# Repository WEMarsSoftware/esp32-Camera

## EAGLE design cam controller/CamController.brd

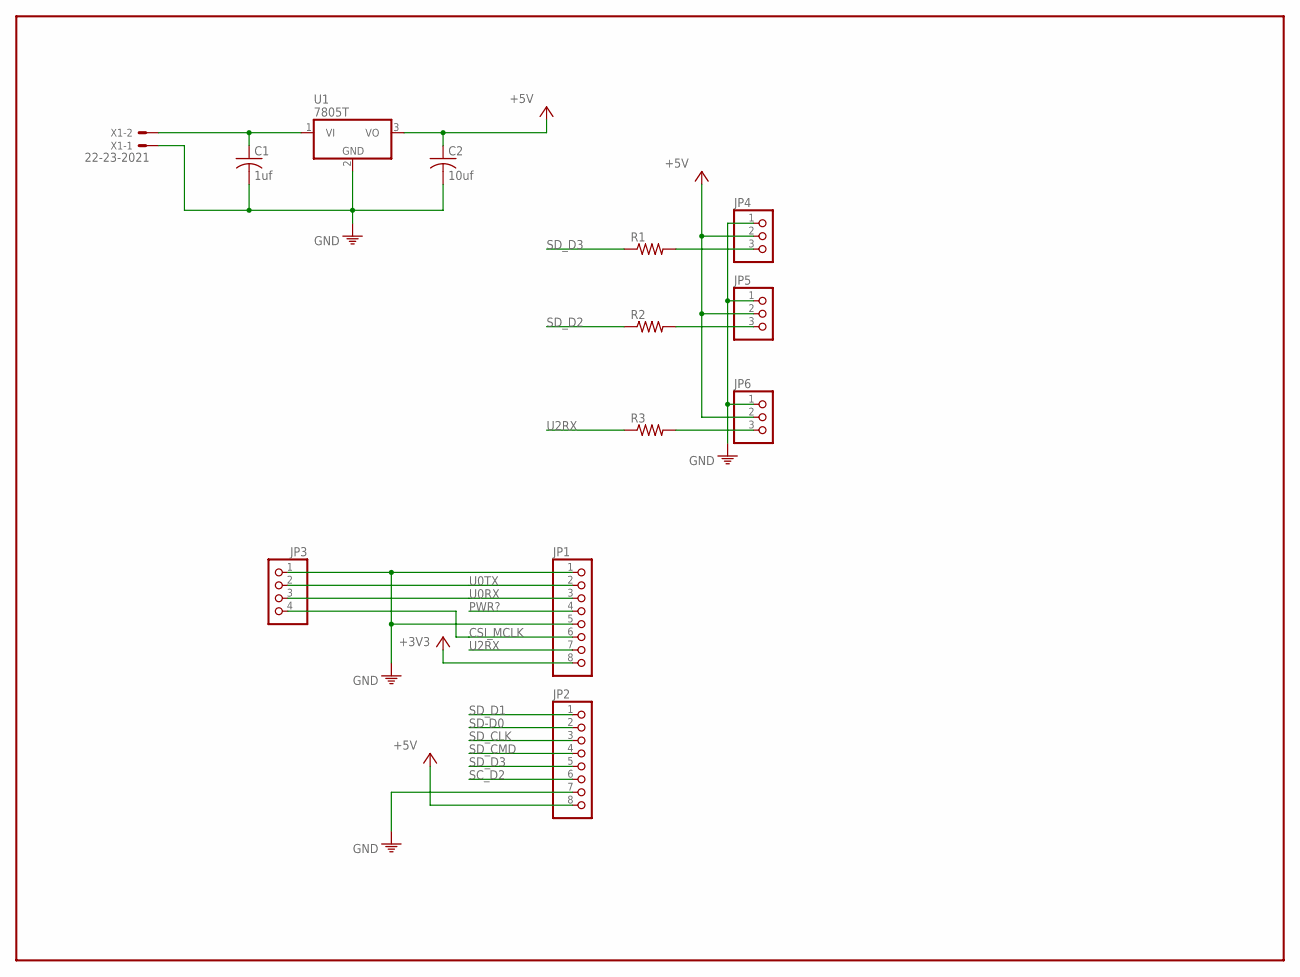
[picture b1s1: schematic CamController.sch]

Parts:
C1: 1uf; C025-040X050
C2: 10uf; C025-030X050
JP1, JP2: PINHD-1X8; 1X08
JP3: PINHD-1X4; 1X04
JP4, JP5, JP6: PINHD-1X3/90; 1X03/90
R1, R2, R3: R-US_0309/10; 0309/10
U1: 7805T; TO220H
X1: 22-23-2021

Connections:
+3V3: JP1.8
+5V: C2.1, JP2.8, JP4.2, JP5.2, JP6.2, U1.3 (VO)
CSI_MCLK: JP1.6, JP3.4
GND: C1.2, C2.2, JP1.1, JP1.5, JP2.7, JP3.1, U1.2 (GND), X1.1
unnamed: C1.1, U1.1 (VI), X1.2
unnamed: JP5.3, R2.2
unnamed: JP6.3, R3.2
PE: JP4.1, JP5.1, JP6.1
PWR?: JP1.4
SC_D2: JP2.6
SD-D0: JP2.2
SD_CLK: JP2.3
SD_CMD: JP2.4
SD_D1: JP2.1
SD_D2: R2.1
SD_D3: JP2.5, JP4.3, R1.1, R1.2
U0RX: JP1.3, JP3.3
U0TX: JP1.2, JP3.2
U2RX: JP1.7, R3.1

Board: 2 copper layers, 13 parts (2 on the bottom side), 11 nets, no tracks yet.

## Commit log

2019-07-13 start with origian CameraWEBSever code : modify to : have two pages one with controls the orther with just full sceen video and one butting to take you back to menu page chk out zooming and cropping
2019-07-15 removed all face recognition information: compiled
2019-08-02 test
2019-08-02 testing img sizing an position
2019-08-02 removve this to se it sizing changes
2019-08-02 made img big but lost controls
2019-08-02 pushed image all the way to right side
2019-08-05 set screen size to fixed size try to make larger smaller and flexable once sizes grow
2019-08-05 set size to fixed max for now to keep every thing in screen also removed some old code and comments to shrink fiel size
2019-08-05 fix stream size chnge x and y servo ranges to 12 to 26 so no convertion is needed start adding in ledcwrite servo control
2019-08-05 servo signals working but did put in zoom problems t=wth thrid ledc command stops streaming. need to test with actual servo to see if going in the correct direction
2019-08-07 fix camera center and turn off debug info
